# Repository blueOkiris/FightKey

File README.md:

# Fight Key

## Description

A keyboard-based fight stick

Version 1:

## Subdirectories

 - pcb - Fight Key KiCAD PCB project

 - pico - Code to upload to the pico within the Fight Key

 - enclosure - model for the 3D printed case for the Fight Key

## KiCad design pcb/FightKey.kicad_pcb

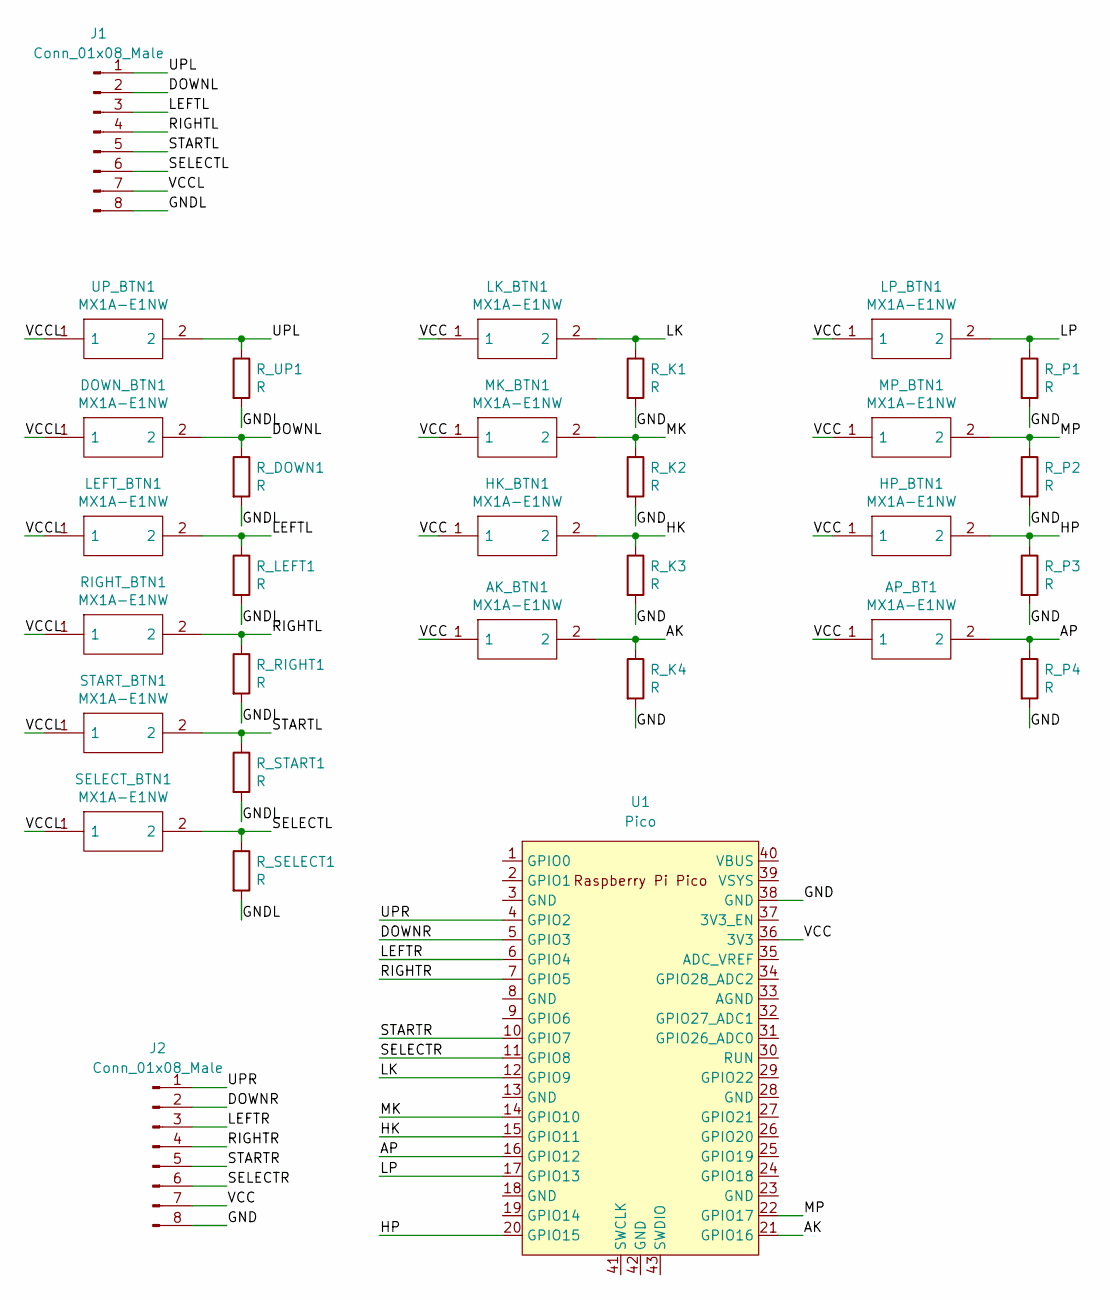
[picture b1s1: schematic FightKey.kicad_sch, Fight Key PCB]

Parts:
AK_BTN1: MX1A-E1NW; MX1AE1NW; Mouser Part Number 540-MX1A-E1NW
AP_BT1: MX1A-E1NW; MX1AE1NW; Mouser Part Number 540-MX1A-E1NW
DOWN_BTN1: MX1A-E1NW; MX1AE1NW; Mouser Part Number 540-MX1A-E1NW
HK_BTN1: MX1A-E1NW; MX1AE1NW; Mouser Part Number 540-MX1A-E1NW
HP_BTN1: MX1A-E1NW; MX1AE1NW; Mouser Part Number 540-MX1A-E1NW
J1, J2: Conn_01x08_Male; PinHeader_1x08_P2.54mm_Vertical
LEFT_BTN1: MX1A-E1NW; MX1AE1NW; Mouser Part Number 540-MX1A-E1NW
LK_BTN1: MX1A-E1NW; MX1AE1NW; Mouser Part Number 540-MX1A-E1NW
LP_BTN1: MX1A-E1NW; MX1AE1NW; Mouser Part Number 540-MX1A-E1NW
MK_BTN1: MX1A-E1NW; MX1AE1NW; Mouser Part Number 540-MX1A-E1NW
MP_BTN1: MX1A-E1NW; MX1AE1NW; Mouser Part Number 540-MX1A-E1NW
RIGHT_BTN1: MX1A-E1NW; MX1AE1NW; Mouser Part Number 540-MX1A-E1NW
R_DOWN1: R; R_Axial_DIN0204_L3.6mm_D1.6mm_P2.54mm_Vertical
R_K1, R_K2, R_K3, R_K4: R; R_Axial_DIN0204_L3.6mm_D1.6mm_P2.54mm_Vertical
R_LEFT1: R; R_Axial_DIN0204_L3.6mm_D1.6mm_P2.54mm_Vertical
R_P1, R_P2, R_P3, R_P4: R; R_Axial_DIN0204_L3.6mm_D1.6mm_P2.54mm_Vertical
R_RIGHT1: R; R_Axial_DIN0204_L3.6mm_D1.6mm_P2.54mm_Vertical
R_SELECT1: R; R_Axial_DIN0204_L3.6mm_D1.6mm_P2.54mm_Vertical
R_START1: R; R_Axial_DIN0204_L3.6mm_D1.6mm_P2.54mm_Vertical
R_UP1: R; R_Axial_DIN0204_L3.6mm_D1.6mm_P2.54mm_Vertical
SELECT_BTN1: MX1A-E1NW; MX1AE1NW; Mouser Part Number 540-MX1A-E1NW
START_BTN1: MX1A-E1NW; MX1AE1NW; Mouser Part Number 540-MX1A-E1NW
U1: Pico; RPi_Pico_SMD_TH
UP_BTN1: MX1A-E1NW; MX1AE1NW; Mouser Part Number 540-MX1A-E1NW

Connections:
/AK: AK_BTN1.2, R_K4.1, U1.21 (GPIO16)
/AP: AP_BT1.2, R_P4.1, U1.16 (GPIO12)
/DOWNL: DOWN_BTN1.2, J1.2, R_DOWN1.1
/DOWNR: J2.2, U1.5 (GPIO3)
/GND: J2.8, R_K1.2, R_K2.2, R_K3.2, R_K4.2, R_P1.2, R_P2.2, R_P3.2, R_P4.2, U1.38 (GND)
/GNDL: J1.8, R_DOWN1.2, R_LEFT1.2, R_RIGHT1.2, R_SELECT1.2, R_START1.2, R_UP1.2
/HK: HK_BTN1.2, R_K3.1, U1.15 (GPIO11)
/HP: HP_BTN1.2, R_P3.1, U1.20 (GPIO15)
/LEFTL: J1.3, LEFT_BTN1.2, R_LEFT1.1
/LEFTR: J2.3, U1.6 (GPIO4)
/LK: LK_BTN1.2, R_K1.1, U1.12 (GPIO9)
/LP: LP_BTN1.2, R_P1.1, U1.17 (GPIO13)
/MK: MK_BTN1.2, R_K2.1, U1.14 (GPIO10)
/MP: MP_BTN1.2, R_P2.1, U1.22 (GPIO17)
/RIGHTL: J1.4, RIGHT_BTN1.2, R_RIGHT1.1
/RIGHTR: J2.4, U1.7 (GPIO5)
/SELECTL: J1.6, R_SELECT1.1, SELECT_BTN1.2
/SELECTR: J2.6, U1.11 (GPIO8)
/STARTL: J1.5, R_START1.1, START_BTN1.2
/STARTR: J2.5, U1.10 (GPIO7)
/UPL: J1.1, R_UP1.1, UP_BTN1.2
/UPR: J2.1, U1.4 (GPIO2)
/VCC: AK_BTN1.1, AP_BT1.1, HK_BTN1.1, HP_BTN1.1, J2.7, LK_BTN1.1, LP_BTN1.1, MK_BTN1.1, MP_BTN1.1, U1.36 (3V3)
/VCCL: DOWN_BTN1.1, J1.7, LEFT_BTN1.1, RIGHT_BTN1.1, SELECT_BTN1.1, START_BTN1.1, UP_BTN1.1

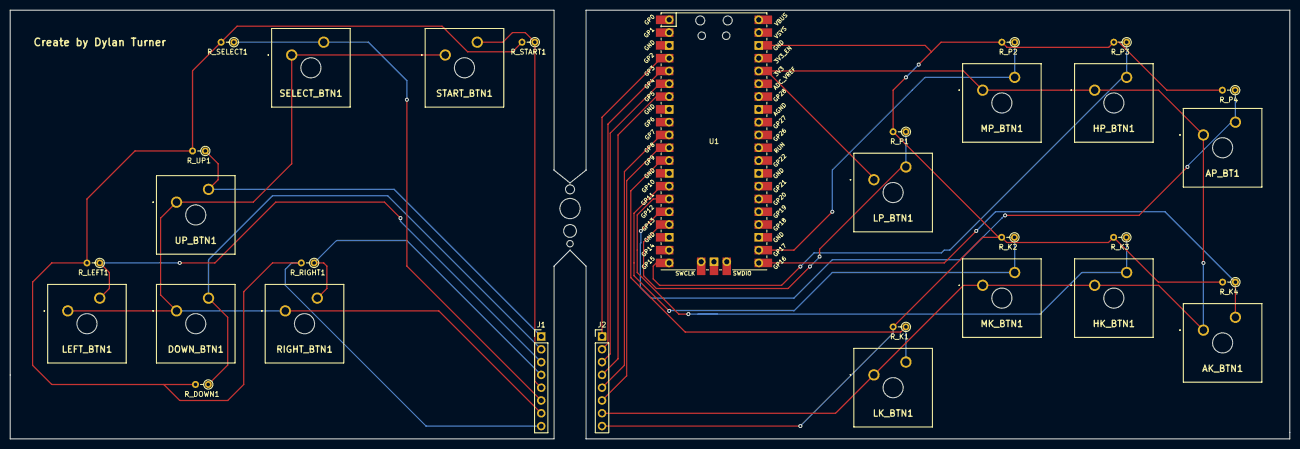
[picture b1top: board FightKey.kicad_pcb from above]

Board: 2 copper layers, 254.0 x 85.1 mm, 31 parts (0 on the bottom side), 24 nets.

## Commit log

2021-09-22 Added current model work and pcb design
2021-09-22 Added code from old version of Game Card (to reuse pico hid stuff
2021-09-23 Adjusted project to get closer to correct format
2021-09-23 Removed links.txt
2021-09-23 Fixed naming convention
2021-09-23 Fixed CmakeLists.txt
2021-09-23 Simplified and corrected makefile
2021-09-23 Fixed main function
2021-09-23 Fixed compilation issues
2021-09-23 Added hid test and used it to improve final functionality
2021-09-23 Deleted pico_sdk_import
2021-09-23 Added button test to verify button functionality.
2021-09-23 Readded readme
2021-09-23 Implemented multiple keys
2021-09-23 Fixed key sendings
2021-09-23 Flipped kicks and punches to match pcb
2021-09-30 Modified select key to send escape since that's more useful in USFIV
2021-09-30 Changed medium punch bc I broke the pin
2021-09-30 Fixed makefile and removed uneeded code
2021-09-30 Added basic idea for enclosure as well as diagram that can be printed out and used to cut out the front panel
2022-01-14 Added enclosure and final picture
2022-01-14 Removed stl files from being added
2022-01-14 Actually removed models
2022-01-14 Removed old blender model
2022-03-07 Renamed cmakelists to proper name:
2022-03-08 Added increasing clock speed to fight key
2022-03-08 Switched to gamepad version
2022-03-08 Fixed controller button mapping
2022-05-22 Remade PCB to be split and include Pico in design
2022-05-24 Removed stray trace
2022-05-24 Restarted enclosure and modeled out new board left side as a reference
2022-05-24 Fixed missing connection (will have to hotwire physically :(
2022-05-24 Added bottom of enclosure (not done) and modeled right pcb board
2022-05-26 Added top-left of enclosure, left-side rounding, and screw holes
2022-05-26 Added top-right and fixed minor issues. Design complete
2022-05-27 Fixed the keybindings to match expected
2022-05-27 Turned off sys clock increase as it seems to break new pico for some reason
2022-05-27 Readded overclocking, but a decreased amount
2022-05-27 Reworked model polish (screw holes and roundedness stuff
2022-05-28 Fixed key bindings
2022-06-05 Updated model to fix print issue and increase screw size on incorrect hole
2022-06-08 Fixed some model issues and finished wide version
2022-06-08 Converted to slimmer, openable model with split design (#1)
    * Remade PCB to be split and include Pico in design
    * Removed stray trace
    * Restarted enclosure and modeled out new board left side as a reference
    * Fixed missing connection (will have to hotwire physically :(
    * Added bottom of enclosure (not done) and modeled right pcb board
    * Added top-left of enclosure, left-side rounding, and screw holes
